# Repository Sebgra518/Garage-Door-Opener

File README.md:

# Smart Garage Door Opener (Hardware Hack + Custom PCB)

A custom hardware interface that integrates a legacy garage door opener with ESP Home automation.  
Designed and built from scratch including schematic design, PCB layout (KiCad), and firmware.

## Demo

TODO: DEMO VIDEO

DODO: Import final PCB Photo

## Problem

My garage door opener had no remote automation capability.  
Commercial solutions were expensive and closed-source.

Goals:
- Integrate with Home Assistant
- Detect when the garage door is open/closed
- Design a test breadbaord setup
- Design a permanent PCB solution

## Hardware Design

### Original Hardware:
- Opens with a button press which is passed through a capacitor. This determins whether to open the door, turn the light on/off, or lock the garage door.
- Garage door opener controls are low voltage and do not draw alot of power

## System Architecture

### Componenets: 
- The ESP32 micrcontroller only consumes around 7W at idle and integrates seemlesly into homeassistant with custom firmware, wifi, and the ability to create custom YAML files to configure pins and button interactions on Homeassistant. 
- MOSFETs can come is very small packages and work perfectly for a voltage controled switch.

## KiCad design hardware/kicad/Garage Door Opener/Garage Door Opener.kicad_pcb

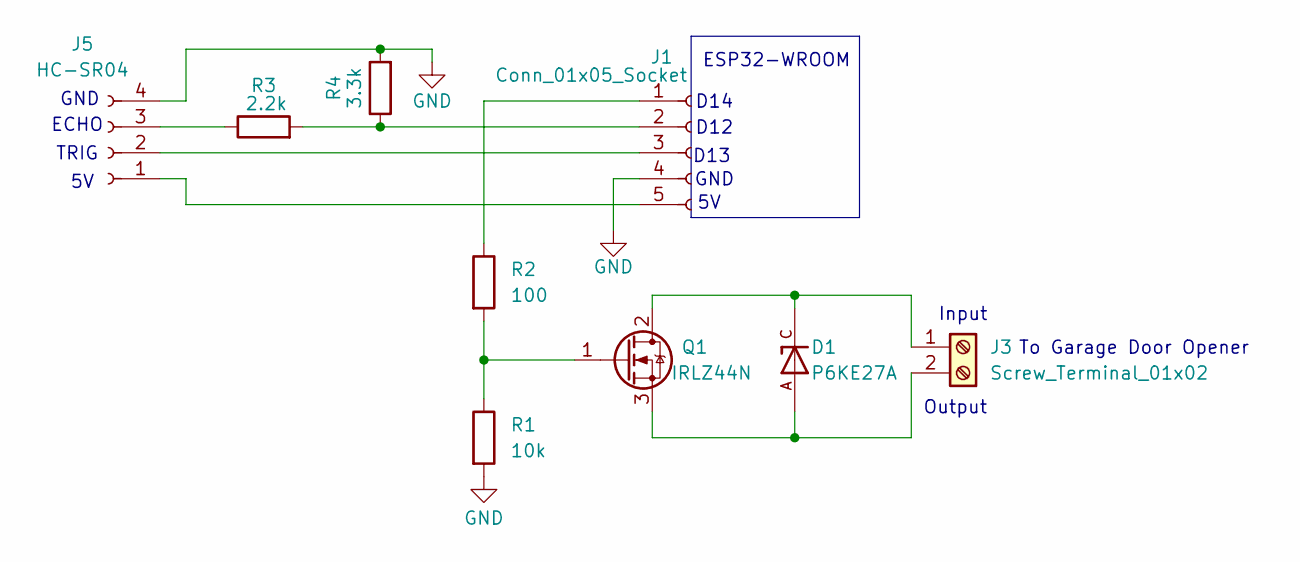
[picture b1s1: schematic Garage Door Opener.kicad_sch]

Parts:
D1: P6KE27A; DIOAD1300W80L670D310; PARTREV K2105
J1: Conn_01x05_Socket; PinSocket_1x05_P2.54mm_Vertical
J3: Screw_Terminal_01x02; TerminalBlock_Phoenix_MKDS-1,5-2-5.08_1x02_P5.08mm_Horizont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
J5: HC-SR04; PinSocket_1x04_P2.54mm_Vertical
Q1: IRLZ44N; TO-220-3_Vertical
R1: 10k; R_Axial_DIN0309_L9.0mm_D3.2mm_P12.70mm_Horizontal
R2: 100; R_Axial_DIN0309_L9.0mm_D3.2mm_P12.70mm_Horizontal
R3: 2.2k; R_Axial_DIN0309_L9.0mm_D3.2mm_P12.70mm_Horizontal
R4: 3.3k; R_Axial_DIN0309_L9.0mm_D3.2mm_P12.70mm_Horizontal

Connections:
GND: J1.4, J5.4, R1.2, R4.2
unnamed: J1.1, R2.1
unnamed: J1.2, R3.2, R4.1
unnamed: J1.3, J5.2
unnamed: J1.5, J5.1
unnamed: D1.C, J3.1, Q1.2 (D)
unnamed: D1.A, J3.2, Q1.3 (S)
unnamed: J5.3, R3.1
unnamed: Q1.1 (G), R1.1, R2.2

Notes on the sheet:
D12
Input
ESP32-WROOM
GND
To Garage Door Opener
Output
D14
GND
D13
TRIG
ECHO

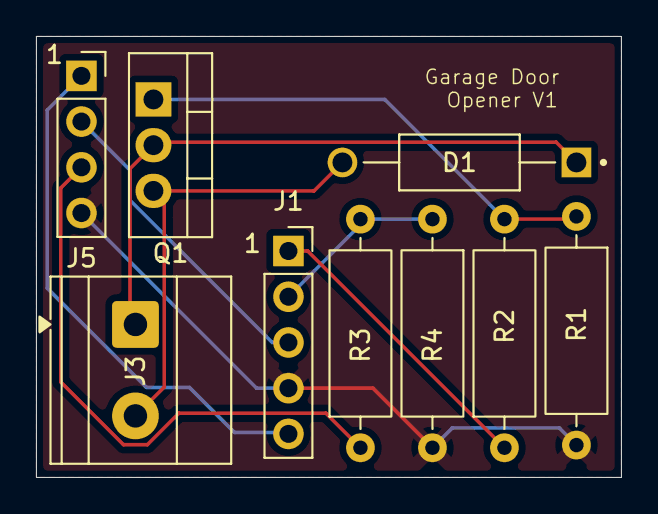
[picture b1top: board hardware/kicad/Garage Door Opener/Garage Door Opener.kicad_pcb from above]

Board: 2 copper layers, 32.5 x 24.5 mm, 9 parts (0 on the bottom side), 9 nets.

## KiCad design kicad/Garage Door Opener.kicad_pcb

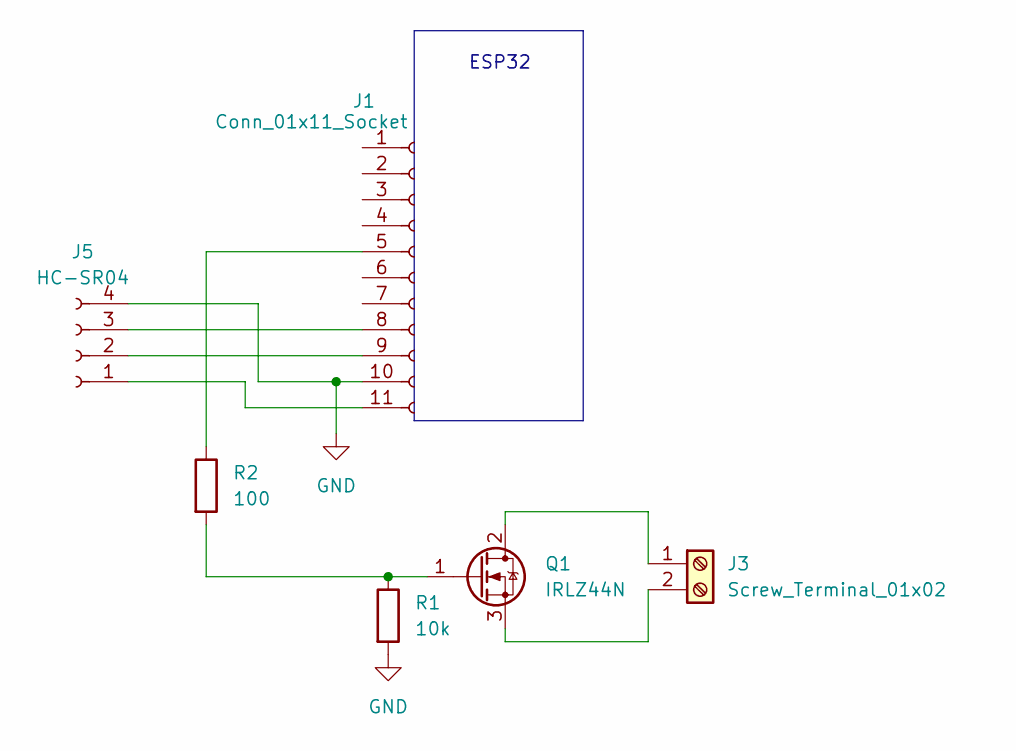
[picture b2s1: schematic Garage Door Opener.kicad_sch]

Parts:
J1: Conn_01x11_Socket; PinSocket_1x11_P2.54mm_Vertical
J3: Screw_Terminal_01x02; TerminalBlock_Phoenix_MKDS-1,5-2-5.08_1x02_P5.08mm_Horizont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
J5: HC-SR04; PinSocket_1x04_P2.54mm_Vertical
Q1: IRLZ44N; TO-220-3_Vertical
R1: 10k; R_Axial_DIN0309_L9.0mm_D3.2mm_P12.70mm_Horizontal
R2: 100; R_Axial_DIN0309_L9.0mm_D3.2mm_P12.70mm_Horizontal

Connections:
GND: J1.10, J5.4, R1.2
unnamed: J1.5, R2.1
unnamed: J1.8, J5.3
unnamed: J1.9, J5.2
unnamed: J1.11, J5.1
unnamed: J3.1, Q1.2 (D)
unnamed: J3.2, Q1.3 (S)
unnamed: Q1.1 (G), R1.1, R2.2

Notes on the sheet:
ESP32

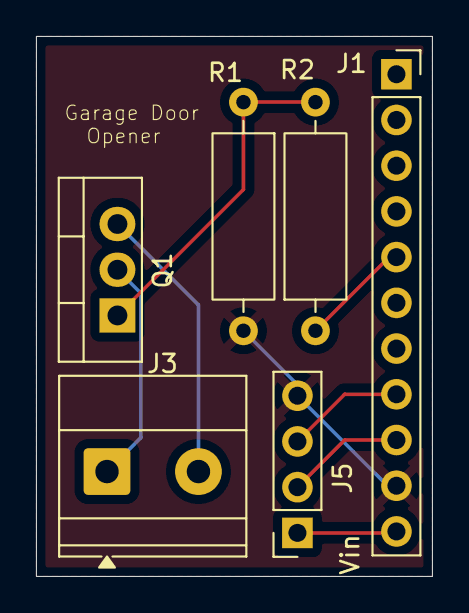
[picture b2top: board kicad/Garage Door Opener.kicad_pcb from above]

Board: 2 copper layers, 22.0 x 30.0 mm, 6 parts (0 on the bottom side), 8 nets.

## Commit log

2026-03-10 Update: Organized Directory
2026-06-11 Added TVS diode and voltage divider for sonar.
